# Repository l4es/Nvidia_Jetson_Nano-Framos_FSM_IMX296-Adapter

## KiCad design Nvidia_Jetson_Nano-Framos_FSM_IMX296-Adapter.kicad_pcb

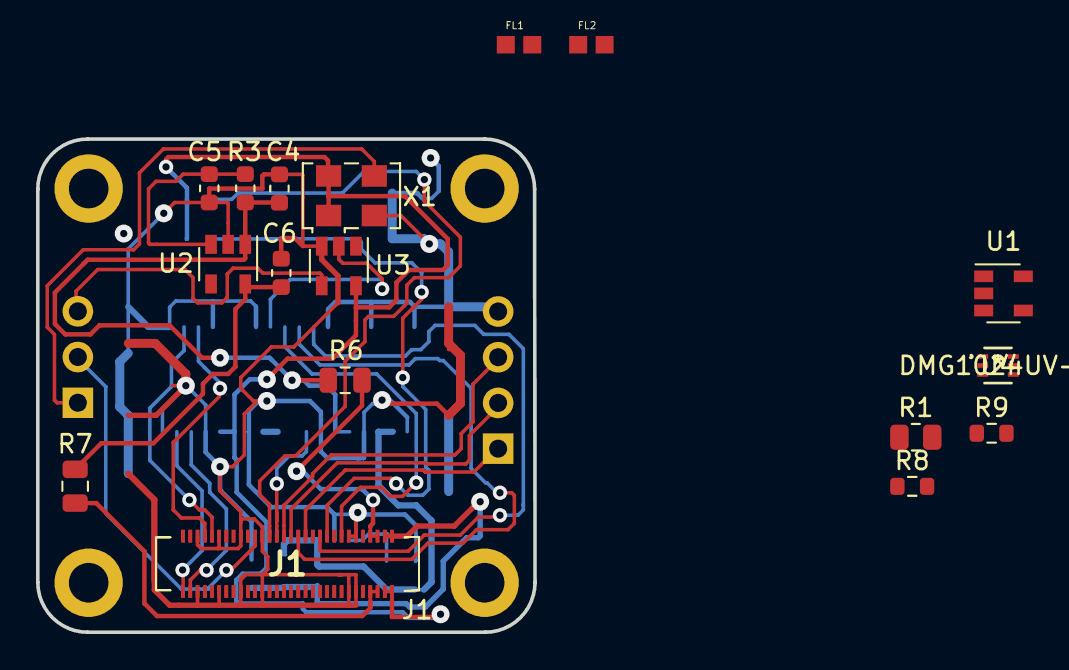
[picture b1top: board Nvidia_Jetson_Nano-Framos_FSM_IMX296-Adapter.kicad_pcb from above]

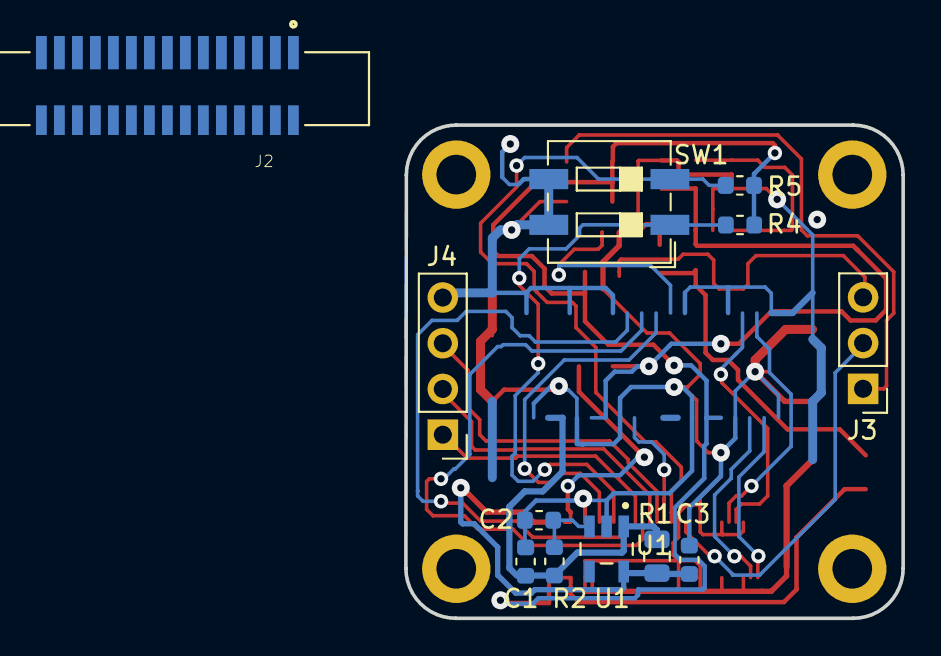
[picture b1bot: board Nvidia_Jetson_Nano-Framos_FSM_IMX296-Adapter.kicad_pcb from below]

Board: 2 copper layers, 27.6 x 27.4 mm, 34 parts (12 on the bottom side), 41 nets.

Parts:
C1, C2, C4, C5: 1uF; C_0603_1608Metric
C3, C6: 10uF; C_0603_1608Metric
FL1, FL2: BLM18AG601SN1D; BEADC1608X95N
J1: DF40HC(4.0)-60DS-0.4V(51); DF40HC4060DS04V51
J1#2: DF40HC_4.0_-60DS-0.4V_51_; DF40HC4060DS04V51
J2: 1-1734248-5; TE_1-1734248-5
J3: CLK_SEL; PinHeader_1x03_P2.54mm_Vertical
J4: EXTENSION; PinHeader_1x04_P2.54mm_Vertical
LD: MountingHole_2.2mm_M2_ISO14580_Pad
LU: MountingHole_2.2mm_M2_ISO14580_Pad
R1, R6, R7: 0; R_0805_2012Metric
R1#2: 22; R_0805_2012Metric
R2, R3: 33k; R_0603_1608Metric
R4, R5: 10k; R_0603_1608Metric
R8, R9: 2k2; R_0603_1608Metric
RD: MountingHole_2.2mm_M2_ISO14580_Pad
RU: MountingHole_2.2mm_M2_ISO14580_Pad
SW1: MASTER_SLAVE; SW_DIP_SPSTx02_Slide_6.7x6.64mm_W6.73mm_P2.54mm_LowProfile_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
U1: LP5907QMFX-3.8Q1; SOT95P280X145-5N
U1#2: LP5907MFX-1.8; SOT-23-5
U2: LP5907MFX-1.2; SOT-23-5
U3: SN74LVC1G14DBV; SOT-23-5
U4: DMG1024UV-7
X1: TXC-7C; Oscillator_SMD_TXC_7C-4Pin_5.0x3.2mm

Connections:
+1V2: C6.1, R7.2, U2.5
+1V8: C3.1, J1.2, J1.4, J1#2.9, R4.2, R5.2, R8.2, R9.1, U1#2.5, U3.5, U4.2, U4.5, X1.1, X1.4
+3V3: FL1.1, FL2.1, J2.15, J2.15_1, R6.1
+3V8: J1.1, J1.3, R1.1, U1.5
+5V: R1.2, U1.1
/CAM_MCLK: J2.12, J2.12_1, U3.2
/CAM_PWDN: C2.1, C5.1, J2.11, J2.11_1, R2.1, R3.1, U1#2.3, U2.3
/CAM_SCL: J2.13, J2.13_1, U4.3
/CAM_SDA: J2.14, J2.14_1, U4.6
/EXT_MCLK: J3.3, U3.4
/GPIO0_XMASTER0: J1.19, J1#2.19, R4.1, SW1.1
/GPIO1_XVS0: J1.25, J1#2.25, J4.1
/GPIO2_XHS0: J1.29, J1#2.29, J4.2
/GPIO3_XTRIG0: J1.31, J1#2.31, J4.3
/GPIO6_SLAMODE: J1.35, J1#2.35, R5.1, SW1.2
/INCK: J1#2.39, J3.2
/INT_MCLK: J3.1, R1#2.2
/MIPI_CSI_CLK0_N__D_CLK_0_N: J1.60, J1#2.60, J2.8, J2.8_1
/MIPI_CSI_CLK0_N__D_CLK_0_P: J2.9, J2.9_1
/MIPI_CSI_CLK0_P__D_CLK_0_P: J1.58, J1#2.58
/MIPI_CSI_D0_N__D_DATA_0_N: J1.51, J1#2.51, J2.2, J2.2_1
/MIPI_CSI_D0_N__D_DATA_0_P: J2.3, J2.3_1
/MIPI_CSI_D0_P__D_DATA_0_P: J1.53, J1#2.53
/SCL_1V8: J1#2.21, R9.2, U4.4
/SDA_1V8: J1#2.27, R8.1, U4.1
GND: C1.2, C2.2, C3.2, C4.2, C5.2, C6.2, J1.11, J1.12, J1.13, J1.14, J1.37, J1.38, J1.43, J1.44, J1.49, J1.50, J1.55, J1.56, J1#2.11, J1#2.12, J1#2.13, J1#2.14, J1#2.37, J1#2.38, J1#2.43, J1#2.44, J1#2.49, J1#2.50, J1#2.55, J1#2.56, J2.1, J2.1_1, J2.4, J2.4_1, J2.7, J2.7_1, J2.10, J2.10_1, J4.4, SW1.3, SW1.4, U1.2, U1#2.2, U2.2, U3.3, X1.2
unnamed: C1.1, FL1.2, R2.2, U1#2.1
unnamed: C4.1, FL2.2, R3.2, U2.1
unnamed: J1.10, J1#2.10
unnamed: J1.46, J1#2.46
unnamed: J1.48, J1#2.48
unnamed: J1.52, J1#2.52
unnamed: J1.54, J1#2.54
unnamed: J1.57, J1#2.57
unnamed: J1.59, J1#2.59
unnamed: J2.5, J2.5_1
unnamed: J2.6, J2.6_1
unnamed: R1#2.1, X1.3
unnamed: U1.4, U1#2.4
VAA: J1.5, J1.7, J1#2.5, J1#2.7, R6.2
VDD: J1.6, J1.8, J1#2.6, J1#2.8, R7.1

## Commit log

2020-11-12 Add schematic and un-routed layout
2020-11-12 Update schematic and layout

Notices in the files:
parts and their libraries:
Copyright 2016 Accelerated Designs. All rights reserved.
